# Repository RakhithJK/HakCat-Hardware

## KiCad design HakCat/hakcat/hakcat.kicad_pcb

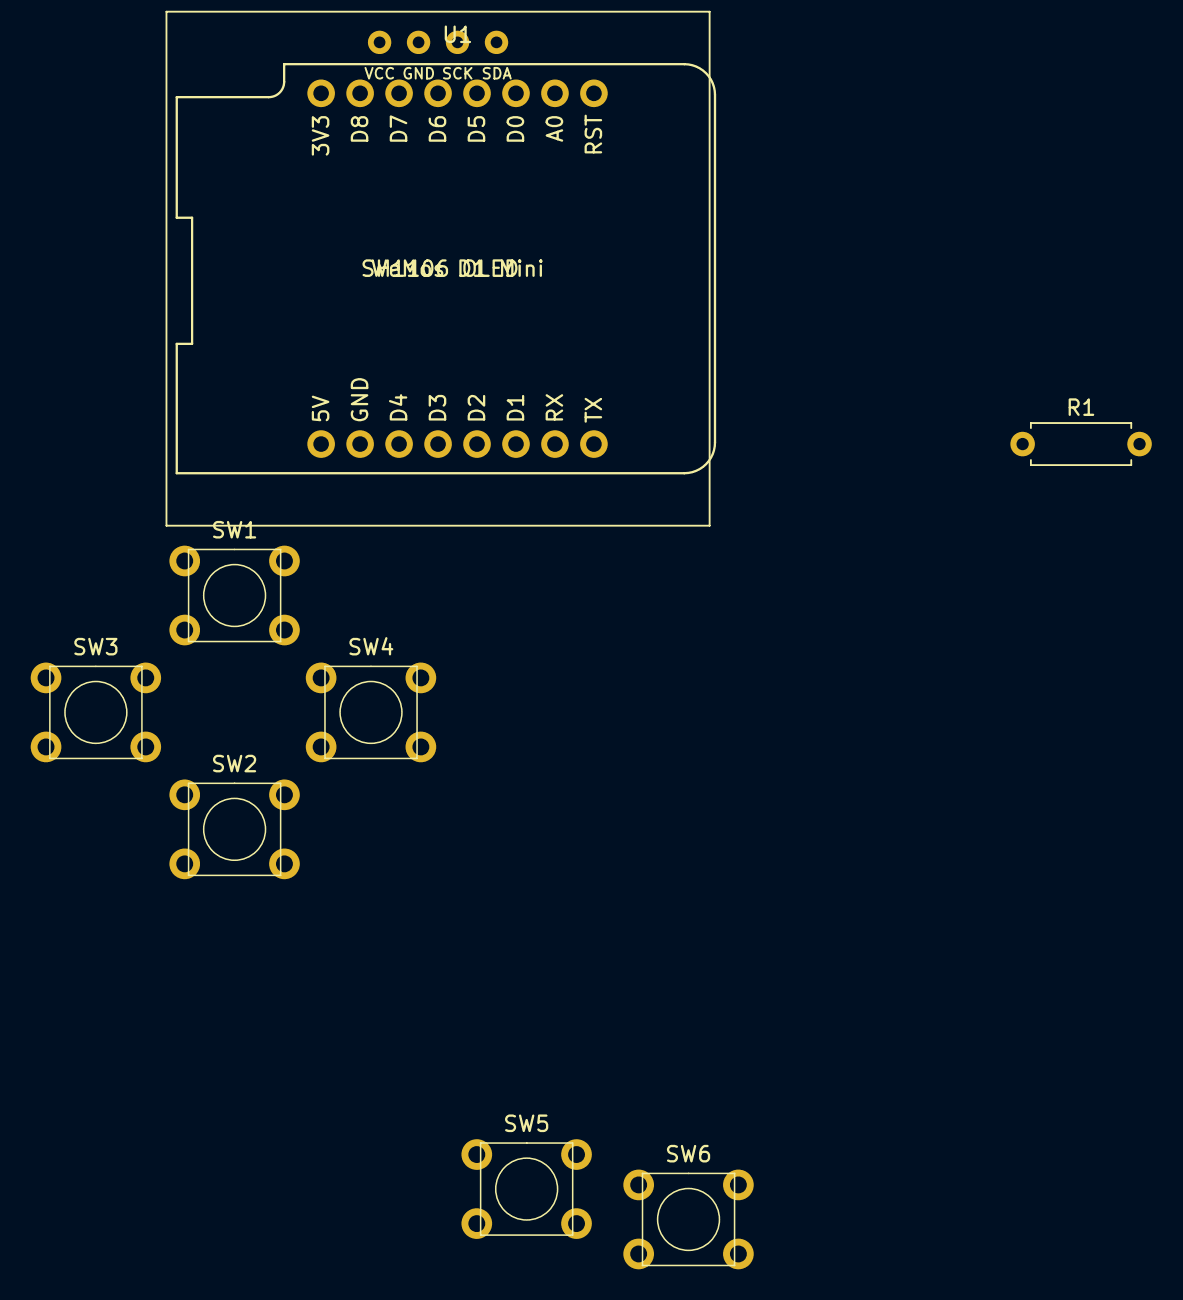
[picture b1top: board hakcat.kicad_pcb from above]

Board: 2 copper layers, 9 parts (0 on the bottom side), 5 nets, no tracks yet.

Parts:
Brd1: SH1106; SH1106-128x64-OLED
R1: 10K; R_Axial_DIN0207_L6.3mm_D2.5mm_P7.62mm_Horizontal
SW1: Up; SW_PUSH_6mm
SW2: Down; SW_PUSH_6mm
SW3: Left; SW_PUSH_6mm
SW4: Right; SW_PUSH_6mm
SW5: A; SW_PUSH_6mm
SW6: B; SW_PUSH_6mm
U1: WeMos D1 Mini; wemos-d1-mini-with-pin-header-and-connector

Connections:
/D0: R1.2, SW2.1
GND: Brd1.1, SW1.2, SW2.2, SW3.2, SW4.2, SW5.2, SW6.2, U1.10
unnamed: Brd1.2, U1.8
unnamed: Brd1.3, U1.14
unnamed: Brd1.4, U1.13

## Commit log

2021-08-06 initialize boards
